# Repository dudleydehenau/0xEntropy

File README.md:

<h1 align="center">0xEntropy</h1>

<p align="center">
  <em>Compact, open-source, USB-powered True Random Number Generator (TRNG) based on Zener diode avalanche breakdown noise and powered by an RP2040.</em>
</p>

---

## Overview

**0xEntropy** is a standalone hardware entropy generator. It harnesses the physical phenomenon of avalanche breakdown in a Zener diode to capture non-deterministic quantum noise, amplifies it, digitizes it at high speed using the Raspberry Pi Pico PIO state machines, and applies real-time SHA-256 cryptographic whitening.

The system features an onboard touchscreen interface, continuous health monitoring, and streams random data over USB.

---

## Features

- **Pure Physical Source**: Avalanche breakdown noise from a reverse-biased 12V Zener diode, filtered and amplified (MCP6002).
- **Filtered Virtual Ground ($V_{REF} = 2.5\text{V}$)**: Strict isolation against USB power rail noise and ripples.
- **Hardware Sampling (PIO)**: High-speed, jitter-free capture offloaded from the CPU.
- **Dual-Core Architecture (RP2040)**:
  - **Core 0**: Touchscreen LCD interface (ultra-lightweight 1-bit bitmap rendering engine), statistics processing, and alerts.
  - **Core 1**: Raw bit acquisition, real-time statistical health tests, and SHA-256 post-processing.
- **Live Monitoring**: Real-time Shannon entropy calculation and physical source health supervision.
- **100% Plug & Play**: Powered and queried via a standard USB port.

---

## Hardware & Schematics (KiCad)

The PCB isolates the sensitive analog front-end (Zener, op-amp, comparator) from the digital domain (RP2040, screen).

### Schematic

### PCB Layout

---

## Enclosure & 3D Design

A custom 3D enclosure was designed to house the main board, the touchscreen display, and provide access to the micro-USB port.

<table>
  <tr>
    <th width="50%" align="center">3D Model</th>
    <th width="50%" align="center">Assembled Prototype</th>
  </tr>
  <tr>
    <td align="center">
      
    </td>
    <td align="center">
      
    </td>
  </tr>
</table>

<p align="center">
  
  <br>
  <em>Enclosure 3D printing timelapse</em>
</p>

*(F3D / STEP source files are available in the `/file3D` directory)*

---

## Firmware Structure

The firmware is written in **C/C++** using the Pico SDK:

- `firmware/0xEntropy.c`: Main entry point, orchestration, and core loop.
- `firmware/Entropy/`: Physical signal sampling and entropy generation routines.
- `firmware/Health/`: Continuous health monitoring (failure detection and drift detection).
- `firmware/Stats/`: Real-time statistical computations on bitstreams.
- `firmware/UI/`: Display drivers and user interface logic.

<p align="center">
  
  <br>
  <em>Simulated values</em>
</p>

---

## Full Prototype Overview

Overall view of the assembled hardware: the operational PCB connected to the touchscreen display.

<p align="center">
  
  <br>
  <em>Final 0xEntropy board assembled and connected to its touchscreen display</em>
</p>

---

## Quick Start

### 1. Flash the RP2040
1. Download the latest `0xEntropy.uf2` binary from the [Releases](../../releases).
2. Hold down the **BOOTSEL** button on the Raspberry Pi Pico and plug it into your computer via USB.
3. Drag and drop the `.uf2` file onto the mounted USB storage volume.

### 2. Stream Random Bytes

The Pico emulates a standard USB CDC serial port.

#### Option A: Using the Python Script (Recommended / Cross-platform)
Handles real-time throughput monitoring, automatic resume on disconnect, and works on Windows, Linux, and macOS:

```bash
# Dependency
pip install pyserial

# Stream data (e.g., capture 100 MB)
python collect.py -p COM4 -s 100000000 -o random.bin
```

#### Option B: Direct Command Line (Linux / macOS)
```bash
# Quick capture of 1 MB
head -c 1M /dev/ttyACM0 > random.bin
```

---

### 3. Verify Entropy Quality

Quick distribution analysis using the standard `ent` tool:

```bash
ent random.bin
```

Comprehensive statistical test battery with **Dieharder**:

```bash
# Run the full test suite (-a) on a binary stream (-g 201)
dieharder -a -g 201 -f random.bin
```

---

## Performance & Validation

The generator has been rigorously tested and validated for statistical randomness at scale.

- **Observed Throughput**: **~1,300 kbps** (~162 KB/s) continuous stream over USB CDC.
- **Post-Processing**: SHA-256 cryptographic whitening. Default 2:1 compression ratio (512:256 bits), user-selectable on-screen (4:1, 8:1, 16:1).

---

### 1. `ent` Test (10 GB Dataset)

Raw distribution analysis performed on a continuous **10 GB** dataset (`10,000,000,000 bytes`):

```text
Entropy = 8.000000 bits per byte.

Optimum compression would reduce the size
of this 10000000000 byte file by 0 percent.

Chi square distribution for 10000000000 samples is 279.96, and randomly
would exceed this value 13.56 percent of the times.

Arithmetic mean value of data bytes is 127.5013 (127.5 = random).
Monte Carlo value for Pi is 3.141522385 (error 0.00 percent).
Serial correlation coefficient is -0.000013 (totally uncorrelated = 0.0).
```

---

### 2. Dieharder Test Suite (10 GB Dataset)

Full results from the **Dieharder v3.31.1** test battery executed against a **10 GB** stream (SHA-256 2:1 ratio):

<details>

<summary><b>Click to view all 86 detailed test results (Dieharder)</b></summary>

| Test Name | ntuple | tsamples | psamples | p-value | Assessment |
| :--- | :---: | :---: | :---: | :---: | :---: |
| `diehard_birthdays` | 0 | 100 | 100 | 0.39466437 | **PASSED** |
| `diehard_operm5` | 0 | 1 000 000 | 100 | 0.07592355 | **PASSED** |
| `diehard_rank_32x32` | 0 | 40 000 | 100 | 0.59062810 | **PASSED** |
| `diehard_rank_6x8` | 0 | 100 000 | 100 | 0.95475163 | **PASSED** |
| `diehard_bitstream` | 0 | 2 097 152 | 100 | 0.40506079 | **PASSED** |
| `diehard_opso` | 0 | 2 097 152 | 100 | 0.88837531 | **PASSED** |
| `diehard_oqso` | 0 | 2 097 152 | 100 | 0.69125958 | **PASSED** |
| `diehard_dna` | 0 | 2 097 152 | 100 | 0.69906629 | **PASSED** |
| `diehard_count_1s_str` | 0 | 256 000 | 100 | 0.39737472 | **PASSED** |
| `diehard_count_1s_byt` | 0 | 256 000 | 100 | 0.92060347 | **PASSED** |
| `diehard_parking_lot` | 0 | 12 000 | 100 | 0.43926798 | **PASSED** |
| `diehard_2dsphere` | 2 | 8 000 | 100 | 0.92344609 | **PASSED** |
| `diehard_3dsphere` | 3 | 4 000 | 100 | 0.96173291 | **PASSED** |
| `diehard_squeeze` | 0 | 100 000 | 100 | 0.79221232 | **PASSED** |
| `diehard_sums` | 0 | 100 | 100 | 0.55542507 | **PASSED** |
| `diehard_runs` | 0 | 100 000 | 100 | 0.13786658 | **PASSED** |
| `diehard_runs` | 0 | 100 000 | 100 | 0.17085449 | **PASSED** |
| `diehard_craps` | 0 | 200 000 | 100 | 0.67687026 | **PASSED** |
| `diehard_craps` | 0 | 200 000 | 100 | 0.91082777 | **PASSED** |
| `marsaglia_tsang_gcd` | 0 | 10 000 000 | 100 | 0.93839213 | **PASSED** |
| `marsaglia_tsang_gcd` | 0 | 10 000 000 | 100 | 0.84764647 | **PASSED** |
| `sts_monobit` | 1 | 100 000 | 100 | 0.28551441 | **PASSED** |
| `sts_runs` | 2 | 100 000 | 100 | 0.29973049 | **PASSED** |
| `sts_serial` | 1 | 100 000 | 100 | 0.45563392 | **PASSED** |
| `sts_serial` | 2 | 100 000 | 100 | 0.14689616 | **PASSED** |
| `sts_serial` | 3 | 100 000 | 100 | 0.16976266 | **PASSED** |
| `sts_serial` | 3 | 100 000 | 100 | 0.58643956 | **PASSED** |
| `sts_serial` | 4 | 100 000 | 100 | 0.62041623 | **PASSED** |
| `sts_serial` | 4 | 100 000 | 100 | 0.93374301 | **PASSED** |
| `sts_serial` | 5 | 100 000 | 100 | 0.42325503 | **PASSED** |
| `sts_serial` | 5 | 100 000 | 100 | 0.96197560 | **PASSED** |
| `sts_serial` | 6 | 100 000 | 100 | 0.21788455 | **PASSED** |
| `sts_serial` | 6 | 100 000 | 100 | 0.69535327 | **PASSED** |
| `sts_serial` | 7 | 100 000 | 100 | 0.03066406 | **PASSED** |
| `sts_serial` | 7 | 100 000 | 100 | 0.01328619 | **PASSED** |
| `sts_serial` | 8 | 100 000 | 100 | 0.62365992 | **PASSED** |
| `sts_serial` | 8 | 100 000 | 100 | 0.28004021 | **PASSED** |
| `sts_serial` | 9 | 100 000 | 100 | 0.90096448 | **PASSED** |
| `sts_serial` | 9 | 100 000 | 100 | 0.97761790 | **PASSED** |
| `sts_serial` | 10 | 100 000 | 100 | 0.51356615 | **PASSED** |
| `sts_serial` | 10 | 100 000 | 100 | 0.64523823 | **PASSED** |
| `sts_serial` | 11 | 100 000 | 100 | 0.93859732 | **PASSED** |
| `sts_serial` | 11 | 100 000 | 100 | 0.32514183 | **PASSED** |
| `sts_serial` | 12 | 100 000 | 100 | 0.19453278 | **PASSED** |
| `sts_serial` | 12 | 100 000 | 100 | 0.35736285 | **PASSED** |
| `sts_serial` | 13 | 100 000 | 100 | 0.41024144 | **PASSED** |
| `sts_serial` | 13 | 100 000 | 100 | 0.52009147 | **PASSED** |
| `sts_serial` | 14 | 100 000 | 100 | 0.63356596 | **PASSED** |
| `sts_serial` | 14 | 100 000 | 100 | 0.05597814 | **PASSED** |
| `sts_serial` | 15 | 100 000 | 100 | 0.44014124 | **PASSED** |
| `sts_serial` | 15 | 100 000 | 100 | 0.17108281 | **PASSED** |
| `sts_serial` | 16 | 100 000 | 100 | 0.83506756 | **PASSED** |
| `sts_serial` | 16 | 100 000 | 100 | 0.92781694 | **PASSED** |
| `rgb_bitdist` | 1 | 100 000 | 100 | 0.50215495 | **PASSED** |
| `rgb_bitdist` | 2 | 100 000 | 100 | 0.67467770 | **PASSED** |
| `rgb_bitdist` | 3 | 100 000 | 100 | 0.68604339 | **PASSED** |
| `rgb_bitdist` | 4 | 100 000 | 100 | 0.63639093 | **PASSED** |
| `rgb_bitdist` | 5 | 100 000 | 100 | 0.00711522 | **PASSED** |
| `rgb_bitdist` | 6 | 100 000 | 100 | 0.03642615 | **PASSED** |
| `rgb_bitdist` | 7 | 100 000 | 100 | 0.54886931 | **PASSED** |
| `rgb_bitdist` | 8 | 100 000 | 100 | 0.94844778 | **PASSED** |
| `rgb_bitdist` | 9 | 100 000 | 100 | 0.80804374 | **PASSED** |
| `rgb_bitdist` | 10 | 100 000 | 100 | 0.76694934 | **PASSED** |
| `rgb_bitdist` | 11 | 100 000 | 100 | 0.55405954 | **PASSED** |
| `rgb_bitdist` | 12 | 100 000 | 100 | 0.79849495 | **PASSED** |
| `rgb_minimum_distance` | 2 | 10 000 | 1000 | 0.38755637 | **PASSED** |
| `rgb_minimum_distance` | 3 | 10 000 | 1000 | 0.93853771 | **PASSED** |
| `rgb_minimum_distance` | 4 | 10 000 | 1000 | 0.63970846 | **PASSED** |
| `rgb_minimum_distance` | 5 | 10 000 | 1000 | 0.33087978 | **PASSED** |
| `rgb_permutations` | 2 | 100 000 | 100 | 0.80472843 | **PASSED** |
| `rgb_permutations` | 3 | 100 000 | 100 | 0.80939095 | **PASSED** |
| `rgb_permutations` | 4 | 100 000 | 100 | 0.64196966 | **PASSED** |
| `rgb_permutations` | 5 | 100 000 | 100 | 0.97396760 | **PASSED** |
| `rgb_lagged_sum` | 0 | 1 000 000 | 100 | 0.29546209 | **PASSED** |
| `rgb_lagged_sum` | 1 | 1 000 000 | 100 | 0.10736047 | **PASSED** |
| `rgb_lagged_sum` | 2 | 1 000 000 | 100 | 0.90786168 | **PASSED** |
| `rgb_lagged_sum` | 3 | 1 000 000 | 100 | 0.03800803 | **PASSED** |
| `rgb_lagged_sum` | 4 | 1 000 000 | 100 | 0.69745767 | **PASSED** |
| `rgb_lagged_sum` | 5 | 1 000 000 | 100 | 0.30052203 | **PASSED** |
| `rgb_lagged_sum` | 6 | 1 000 000 | 100 | 0.81286624 | **PASSED** |
| `rgb_lagged_sum` | 7 | 1 000 000 | 100 | 0.79490517 | **PASSED** |
| `rgb_lagged_sum` | 8 | 1 000 000 | 100 | 0.85376675 | **PASSED** |
| `rgb_lagged_sum` | 9 | 1 000 000 | 100 | 0.46383055 | **PASSED** |
| `rgb_lagged_sum` | 10 | 1 000 000 | 100 | 0.63063661 | **PASSED** |
| `rgb_lagged_sum` | 11 | 1 000 000 | 100 | 0.39341615 | **PASSED** |
| `rgb_lagged_sum` | 12 | 1 000 000 | 100 | 0.21353291 | **PASSED** |
| `rgb_lagged_sum` | 13 | 1 000 000 | 100 | 0.73964502 | **PASSED** |
| `rgb_lagged_sum` | 14 | 1 000 000 | 100 | 0.76922594 | **PASSED** |
| `rgb_lagged_sum` | 15 | 1 000 000 | 100 | 0.55600967 | **PASSED** |
| `rgb_lagged_sum` | 16 | 1 000 000 | 100 | 0.59271918 | **PASSED** |
| `rgb_lagged_sum` | 17 | 1 000 000 | 100 | 0.90342589 | **PASSED** |
| `rgb_lagged_sum` | 18 | 1 000 000 | 100 | 0.59641374 | **PASSED** |
| `rgb_lagged_sum` | 19 | 1 000 000 | 100 | 0.59765640 | **PASSED** |
| `rgb_lagged_sum` | 20 | 1 000 000 | 100 | 0.52991615 | **PASSED** |
| `rgb_lagged_sum` | 21 | 1 000 000 | 100 | 0.44300317 | **PASSED** |
| `rgb_lagged_sum` | 22 | 1 000 000 | 100 | 0.94796060 | **PASSED** |
| `rgb_lagged_sum` | 23 | 1 000 000 | 100 | 0.20987094 | **PASSED** |
| `rgb_lagged_sum` | 24 | 1 000 000 | 100 | 0.36604221 | **PASSED** |
| `rgb_lagged_sum` | 25 | 1 000 000 | 100 | 0.28560285 | **PASSED** |
| `rgb_lagged_sum` | 26 | 1 000 000 | 100 | 0.52958989 | **PASSED** |
| `rgb_lagged_sum` | 27 | 1 000 000 | 100 | 0.17134459 | **PASSED** |
| `rgb_lagged_sum` | 28 | 1 000 000 | 100 | 0.99634800 | *WEAK* |
| `rgb_lagged_sum` | 29 | 1 000 000 | 100 | 0.36655513 | **PASSED** |
| `rgb_lagged_sum` | 30 | 1 000 000 | 100 | 0.16353244 | **PASSED** |
| `rgb_lagged_sum` | 31 | 1 000 000 | 100 | 0.36323221 | **PASSED** |
| `rgb_lagged_sum` | 32 | 1 000 000 | 100 | 0.67537924 | **PASSED** |
| `rgb_kstest_test` | 0 | 10 000 | 1000 | 0.60363864 | **PASSED** |
| `dab_bytedistrib` | 0 | 51 200 000 | 1 | 0.70763534 | **PASSED** |
| `dab_dct` | 256 | 50 000 | 1 | 0.18425080 | **PASSED** |
| `dab_filltree` | 32 | 15 000 000 | 1 | 0.80178758 | **PASSED** |
| `dab_filltree` | 32 | 15 000 000 | 1 | 0.26571865 | **PASSED** |
| `dab_filltree2` | 0 | 5 000 000 | 1 | 0.69465598 | **PASSED** |
| `dab_filltree2` | 1 | 5 000 000 | 1 | 0.71074721 | **PASSED** |
| `dab_monobit2` | 12 | 65 000 000 | 1 | 0.57586976 | **PASSED** |

</details>

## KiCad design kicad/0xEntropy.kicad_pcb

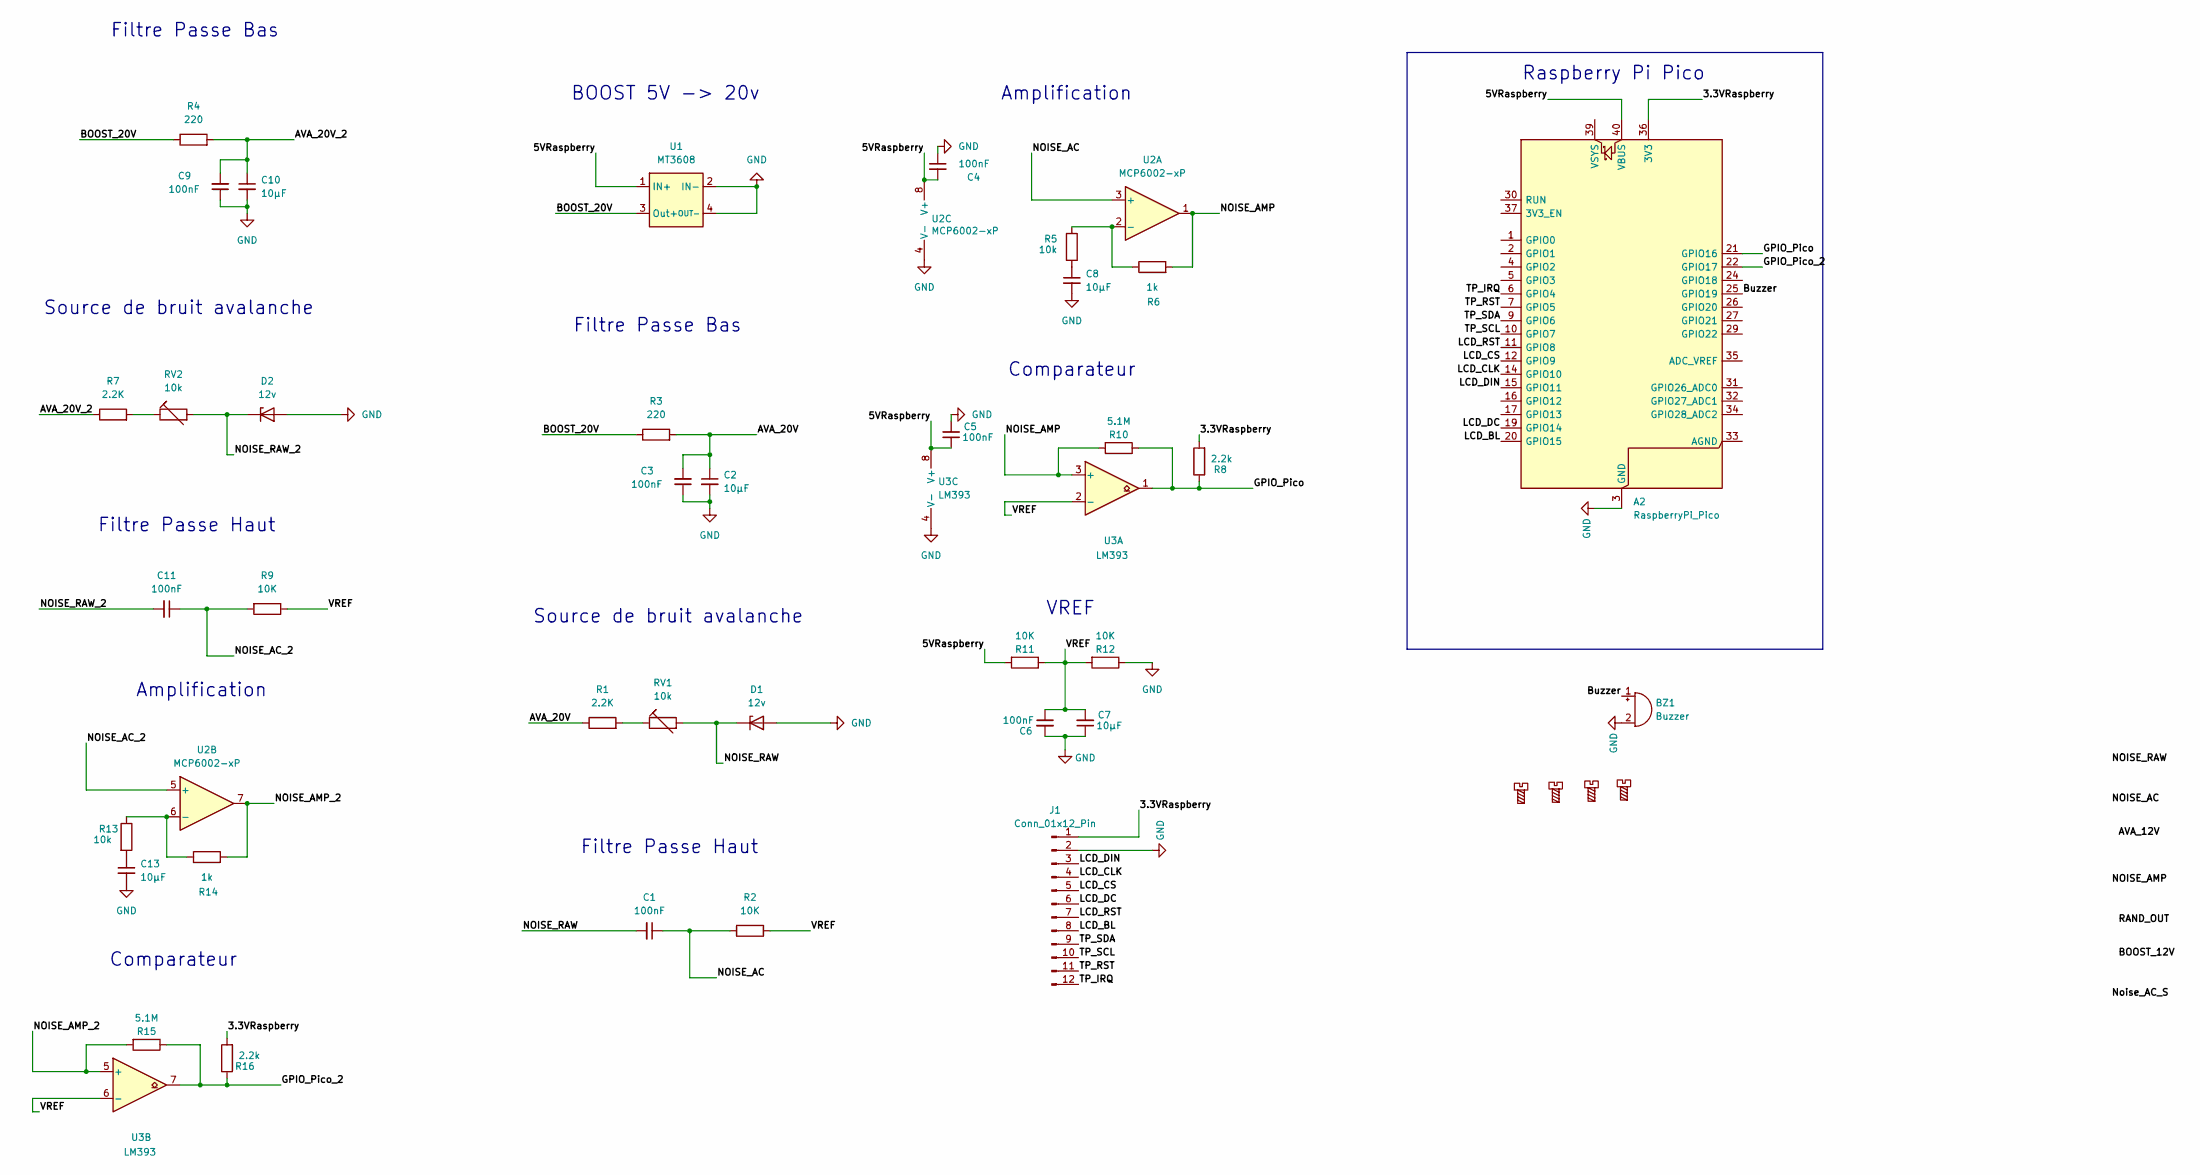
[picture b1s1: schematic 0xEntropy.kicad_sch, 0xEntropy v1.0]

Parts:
A2: RaspberryPi_Pico; RaspberryPi_Pico_Common_Unspecified
BZ1: Buzzer; Buzzer_12x9.5RM7.6
C1, C3, C4, C5, C6, C9, C11: 100nF; C_Disc_D5.0mm_W2.5mm_P5.00mm
C2, C7, C8, C10, C13: 10µF; CP_Radial_D5.0mm_P2.50mm
D1, D2: 12v; D_DO-35_SOD27_P7.62mm_Horizontal
H1, H2, H3, H4: MountingScrew; MountingHole_2.2mm_M2
J1: Conn_01x12_Pin; PinHeader_1x12_P2.54mm_Vertical
R1, R7: 2.2K; R_Axial_DIN0207_L6.3mm_D2.5mm_P10.16mm_Horizontal
R2, R9, R11, R12: 10K; R_Axial_DIN0207_L6.3mm_D2.5mm_P10.16mm_Horizontal
R3, R4: 220; R_Axial_DIN0207_L6.3mm_D2.5mm_P10.16mm_Horizontal
R5, R13: 10k; R_Axial_DIN0207_L6.3mm_D2.5mm_P10.16mm_Horizontal
R6, R14: 1k; R_Axial_DIN0207_L6.3mm_D2.5mm_P10.16mm_Horizontal
R8, R16: 2.2k; R_Axial_DIN0207_L6.3mm_D2.5mm_P10.16mm_Horizontal
R10, R15: 5.1M; R_Axial_DIN0207_L6.3mm_D2.5mm_P10.16mm_Horizontal
RV1, RV2: 10k; Potentiometer_Vishay_T93YA_Vertical
U1: MT3608
U2: MCP6002-xP; DIP-8_W7.62mm
U3: LM393; DIP-8_W7.62mm

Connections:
/3.3VRaspberry: A2.36 (3V3), J1.1, R8.2, R16.2
/5VRaspberry: A2.40 (VBUS), C4.2, C5.1, R11.2, U1.1 (IN+), U2.8 (V+), U3.8 (V+)
/AVA_20V: C2.1, C3.2, R1.1, R3.2
/AVA_20V_2: C9.2, C10.1, R4.2, R7.1
/BOOST_20V: R3.1, R4.1, U1.3 (Out+)
/Buzzer: A2.25 (GPIO19), BZ1.1 (+)
/GPIO_Pico: A2.21 (GPIO16), R8.1, R10.1, U3.1
/GPIO_Pico_2: A2.22 (GPIO17), R15.1, R16.1, U3.7
/LCD_BL: A2.20 (GPIO15), J1.8
/LCD_CLK: A2.14 (GPIO10), J1.4
/LCD_CS: A2.12 (GPIO9), J1.5
/LCD_DC: A2.19 (GPIO14), J1.6
/LCD_DIN: A2.15 (GPIO11), J1.3
/LCD_RST: A2.11 (GPIO8), J1.7
/NOISE_AC: C1.1, R2.2, U2.3 (+)
/NOISE_AC_2: C11.1, R9.2, U2.5 (+)
/NOISE_AMP: R6.2, R10.2, U2.1, U3.3 (+)
/NOISE_AMP_2: R14.2, R15.2, U2.7, U3.5 (+)
/NOISE_RAW: C1.2, D1.1 (K), RV1.2
/NOISE_RAW_2: C11.2, D2.1 (K), RV2.2
/TP_IRQ: A2.6 (GPIO4), J1.12
/TP_RST: A2.7 (GPIO5), J1.11
/TP_SCL: A2.10 (GPIO7), J1.10
/TP_SDA: A2.9 (GPIO6), J1.9
/VREF: C6.1, C7.2, R2.1, R9.1, R11.1, R12.2, U3.2 (-), U3.6 (-)
GND: A2.3 (GND), A2.8 (GND), A2.13 (GND), A2.18 (GND), A2.23 (GND), A2.28 (GND), A2.38 (GND), BZ1.2 (-), C2.2, C3.1, C4.1, C5.2, C6.2, C7.1, C8.2, C9.1, C10.2, C13.2, D1.2 (A), D2.2 (A), J1.2, R12.1, U1.2 (IN-), U1.4 (OUT-), U2.4 (V-), U3.4 (V-)
unnamed: C8.1, R5.2
unnamed: C13.1, R13.2
unnamed: R1.2, RV1.1
unnamed: R7.2, RV2.1
unnamed: R5.1, R6.1, U2.2 (-)
unnamed: R13.1, R14.1, U2.6 (-)

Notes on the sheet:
Amplification
Source de bruit avalanche
Filtre Passe Bas
Comparateur
Filtre Passe Haut
VREF
BOOST 5V -> 20v
Raspberry Pi Pico

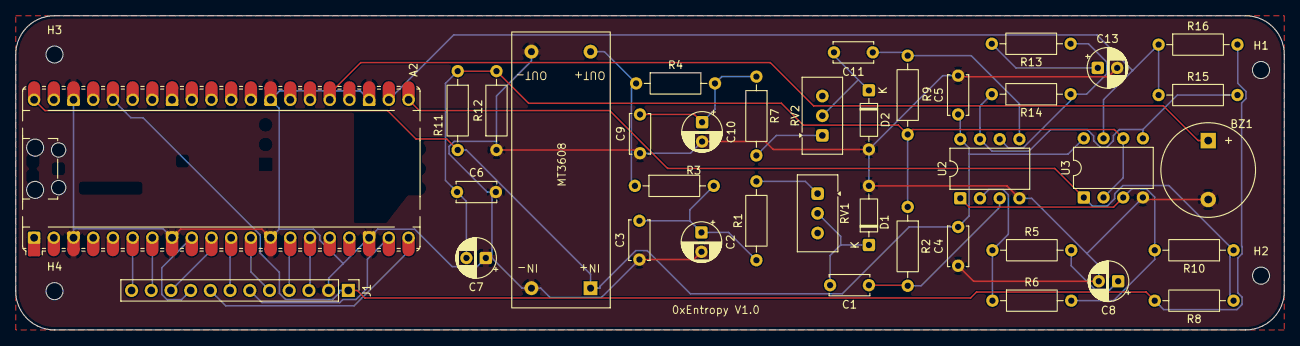
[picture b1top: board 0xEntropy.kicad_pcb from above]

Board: 2 copper layers, 163.5 x 40.5 mm, 42 parts (0 on the bottom side), 32 nets.

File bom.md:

# Bill of Materials (BOM) — OxEntropy

| Réf. Schéma | Qté | Valeur / Désignation | Fabricant | Réf. Fabricant / Commande | Empreinte / Package |
| :--- | :---: | :--- | :--- | :--- | :--- |
| **A2** | 1 | Raspberry Pi Pico | Raspberry Pi | Raspberry Pi Pico | Module Pico THT |
| **BZ1** | 1 | Buzzer 12x9.5 RM7.6 | — | Buzzer THT | Buzzer_12x9.5RM7.6 |
| **C1, C3–C6, C9, C11** | 7 | 100nF | — | Céramique multicouche | C_Disc_D5.0mm_P5.00mm |
| **C2, C7, C8, C10, C13** | 5 | 10µF | — | Électrolytique Radial | CP_Radial_D5.0mm_P2.50mm |
| **D1, D2** | 2 | Diode Zener 12V | Nexperia | BZX79-C12 | DO-35 (SOD27) THT |
| **J1** | 1 | Connecteur 1x12 broches | — | Pin Header 2.54mm | PinHeader_1x12_P2.54mm_Vertical |
| **R1, R7, R8, R16** | 4 | 2.2kΩ | — | Résistance traversante 1/4W | R_Axial_DIN0207_P10.16mm |
| **R2, R5, R9, R11–R13** | 6 | 10kΩ | — | Résistance traversante 1/4W | R_Axial_DIN0207_P10.16mm |
| **R3, R4** | 2 | 220Ω | — | Résistance traversante 1/4W | R_Axial_DIN0207_P10.16mm |
| **R6, R14** | 2 | 1kΩ | — | Résistance traversante 1/4W | R_Axial_DIN0207_P10.16mm |
| **R10, R15** | 2 | 5.1MΩ | — | Résistance traversante 1/4W | R_Axial_DIN0207_P10.16mm |
| **RV1, RV2** | 2 | Potentiomètre 10kΩ | Vishay | T93YA103K | Vishay T93YA Vertical |
| **U1** | 1 | MT3608 (Module Step-Up) | Olimex / Generic | MT3608 | Module Perso:MT3608 |
| **U2** | 1 | MCP6002-E/P (Ampli Op) | Microchip | MCP6002-E/P | DIP-8 (W7.62mm) |
| **U3** | 1 | LM393P (Comparateur) | Texas Instruments | LM393P | DIP-8 (W7.62mm) |
